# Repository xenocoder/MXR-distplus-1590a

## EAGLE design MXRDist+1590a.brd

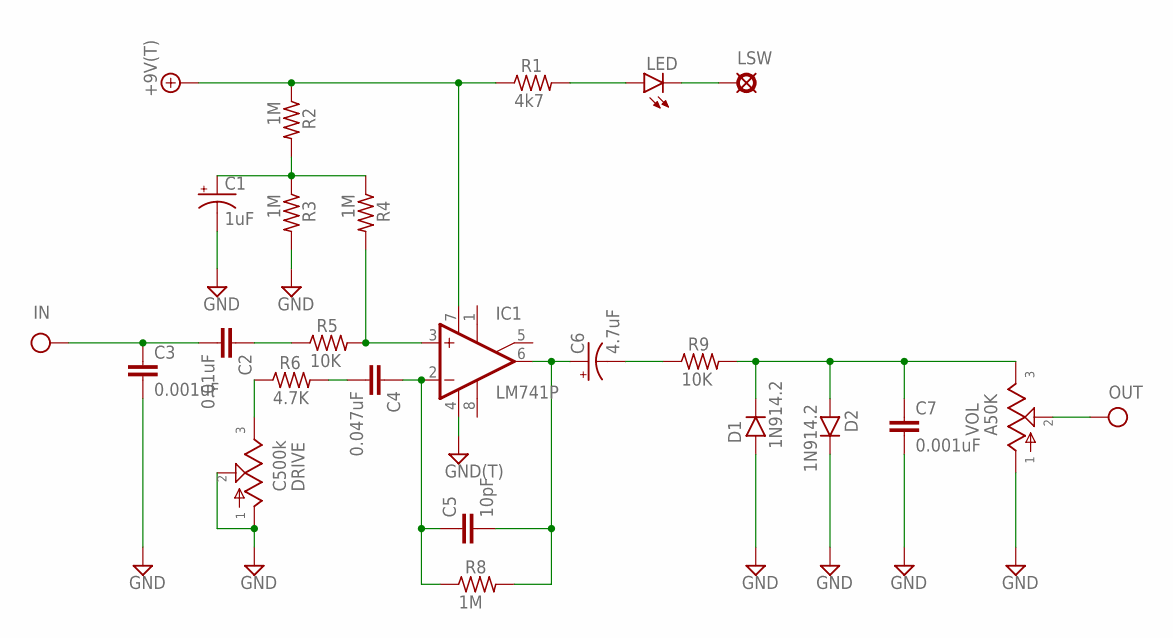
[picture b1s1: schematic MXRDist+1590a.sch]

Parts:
+9V: +9V(T); SQUARE
C1: 1uF; 044A
C2: 0.01uF; 070X030
C3, C7: 0.001uF; 070X030
C4: 0.047uF; 070X030
C5: 10pF; 050X030_050_1
C6: 4.7uF; 044A
D1, D2: 1N914.2; DO35-2
DRIVE: C500k; POT_9MM_PACK
GND: GND(T); SQUARE
IC1: LM741P; DIL08
IN: IN(T); SQUARE
LED: LED3MM
LSW: PAD; SQUARE
OUT: OUT(T); SQUARE
R1: 4k7; R0207/1V
R2, R3, R4, R8: 1M; R0207/1V
R5, R9: 10K; R0207/1V
R6: 4.7K; R0207/1V
VOL: A50K; POT_9MM_PACK

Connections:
+9V: +9V.1, IC1.7 (V+), R1.1, R2.1
GND: C1.2 (-), C3.2, C7.2, D1.A, D2.C, DRIVE.P$1, DRIVE.P$2, GND.1, IC1.4 (V-), R3.2, VOL.P$1
IN: C2.2, C3.1, IN.1
unnamed: C1.1 (+), R2.2, R3.1, R4.1
unnamed: IC1.3 (+IN), R4.2, R5.2
unnamed: C2.1, R5.1
unnamed: DRIVE.P$3, R6.1
unnamed: C5.2, C6.1 (+), IC1.6 (OUT), R8.2
unnamed: C4.2, R6.2
unnamed: C4.1, C5.1, IC1.2 (-IN), R8.1
unnamed: C6.2 (-), R9.1
unnamed: C7.1, D1.C, D2.A, R9.2, VOL.P$3
unnamed: LED.A, R1.2
unnamed: LED.K (C), LSW.1
OUT: OUT.1, VOL.P$2

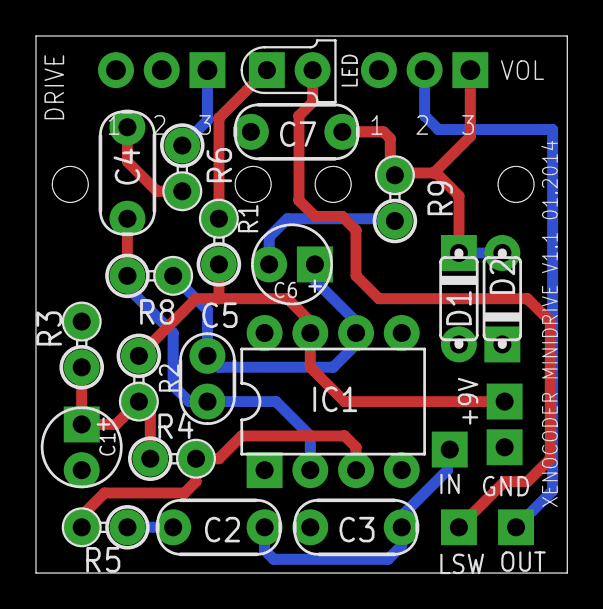
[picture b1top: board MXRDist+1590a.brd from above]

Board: 2 copper layers, 29.5 x 29.8 mm, 26 parts (0 on the bottom side), 15 nets.

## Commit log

2015-10-08 Initial upload
2015-10-08 New layout
